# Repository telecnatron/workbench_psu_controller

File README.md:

# workbench_psu_controller
PSU controller comprising kicad PCB files, AVR C source files, python
utilities

see: https://telecnatron.com/articles/Workbench-Variable-PSU-15V-1A/index.html
for full details.

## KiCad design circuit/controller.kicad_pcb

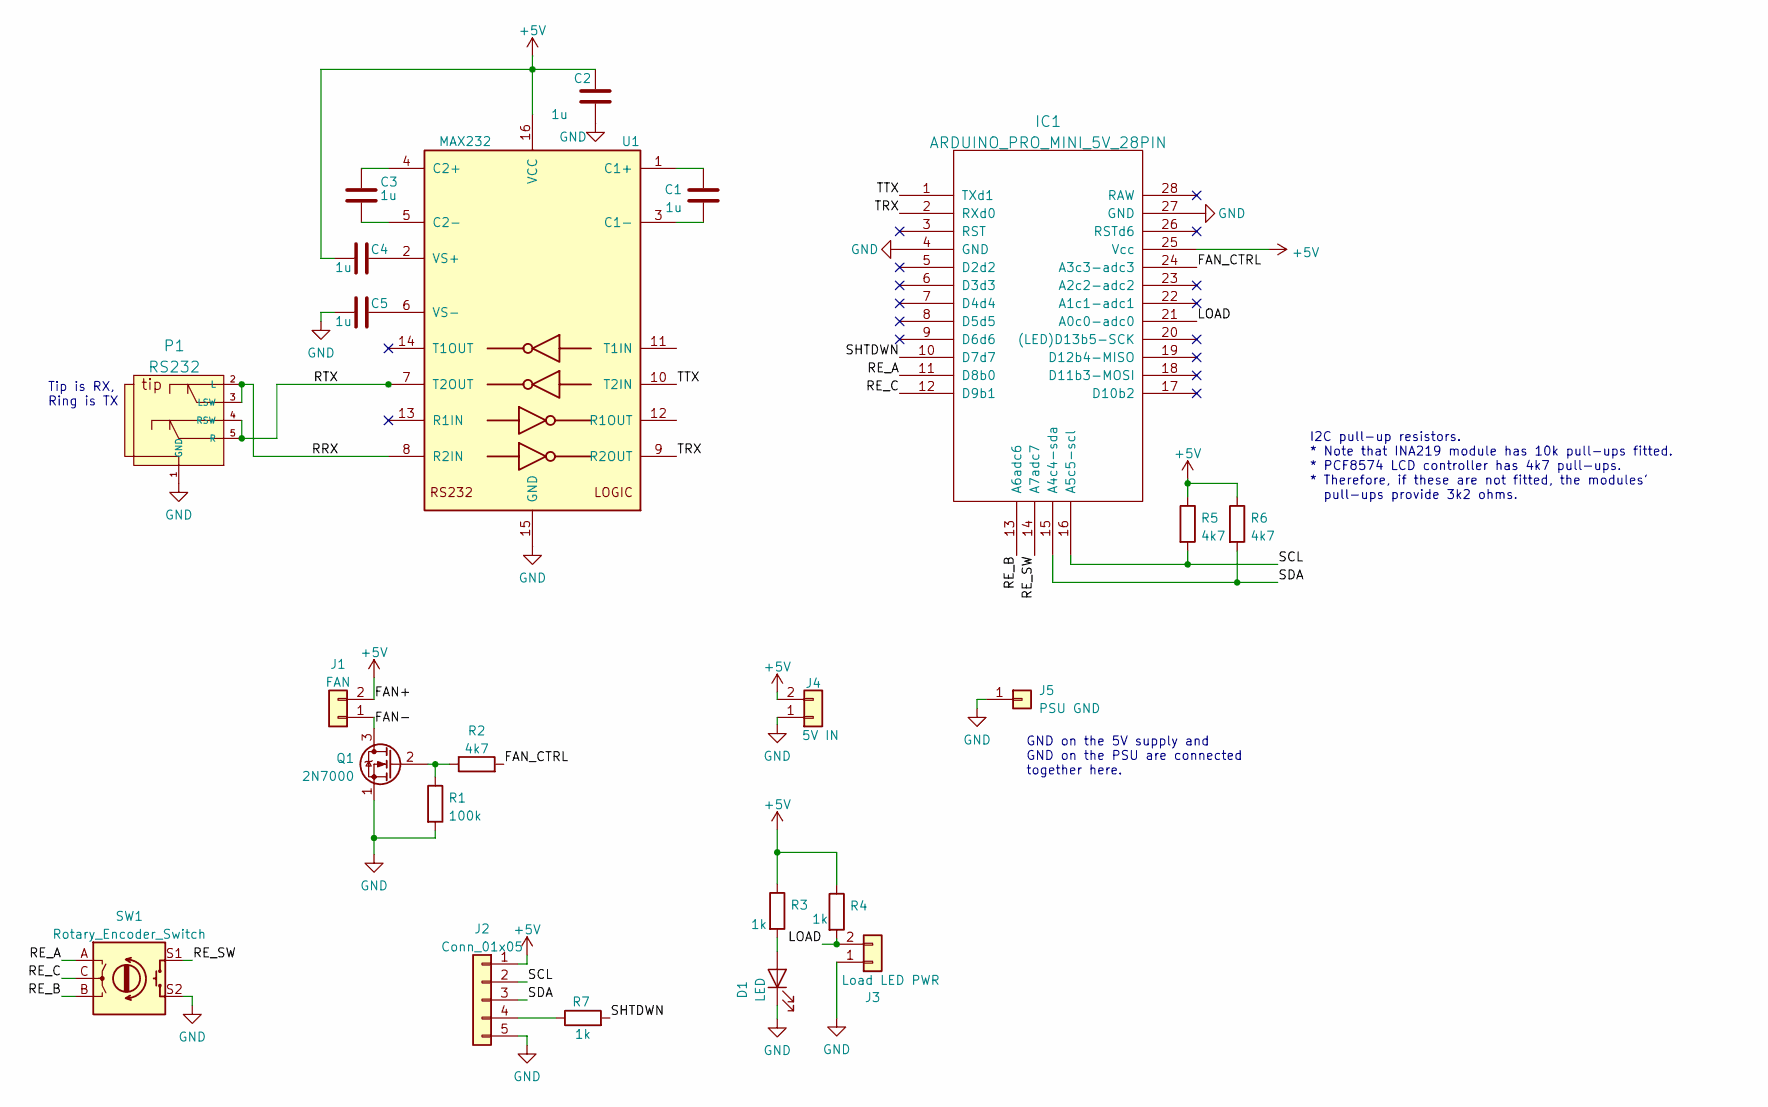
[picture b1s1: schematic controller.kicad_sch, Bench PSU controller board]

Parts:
C1, C2, C3, C4, C5: 1u; C_Disc_D6.0mm_W2.5mm_P5.00mm
D1: LED; JST_XH_B02B-XH-A_1x02_P2.50mm_Vertical
IC1: ARDUINO_PRO_MINI_5V_28PIN; DIP-28_W15.24mm_LongPads
J1: FAN; JST_XH_B02B-XH-A_1x02_P2.50mm_Vertical
J2: Conn_01x05; PinHeader_1x05_P2.54mm_Vertical
J3: Load LED PWR; JST_XH_B02B-XH-A_1x02_P2.50mm_Vertical
J4: 5V IN; JST_XH_B02B-XH-A_1x02_P2.50mm_Vertical
J5: PSU GND; PinHeader_1x01_P2.54mm_Vertical
P1: RS232; JACK-STEREO-3.5mm-PCB-HandSoldered
Q1: 2N7000; TO-92_Inline_Wide
R1: 100k; R_Axial_250mw_DIN0207_L6.3mm_D2.5mm_P10.16mm_Horizontal
R2, R5, R6: 4k7; R_Axial_250mw_DIN0207_L6.3mm_D2.5mm_P10.16mm_Horizontal
R3, R4, R7: 1k; R_Axial_250mw_DIN0207_L6.3mm_D2.5mm_P10.16mm_Horizontal
SW1: Rotary_Encoder_Switch; JST_XH_B5B-XH-AM_1x05_P2.50mm_Vertical_Rotary-Encoder
U1: MAX232; DIP-16_W7.62mm_Socket

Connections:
+5V: C2.1, C4.2, IC1.25 (Vcc), J1.2, J2.1, J4.2, R3.1, R4.1, R5.1, R6.1, U1.16 (VCC)
/FAN-: J1.1, Q1.3 (D)
/FAN_CTRL: IC1.24 (A3c3-adc3), R2.2
/LOAD: IC1.21 (A0c0-adc0), J3.2, R4.2
/RE_A: IC1.11 (D8b0), SW1.A (1)
/RE_B: IC1.13 (A6adc6), SW1.B (3)
/RE_C: IC1.12 (D9b1), SW1.C (2)
/RE_SW: IC1.14 (A7adc7), SW1.S1 (4)
/RRX: P1.2 (L), P1.3 (LSW), U1.8 (R2IN)
/RTX: P1.4 (RSW), P1.5 (R), U1.7 (T2OUT)
/SCL: IC1.16 (A5c5-scl), J2.2, R5.2
/SDA: IC1.15 (A4c4-sda), J2.3, R6.2
/SHTDWN: IC1.10 (D7d7), R7.2
/TRX: IC1.2 (RXd0), U1.9 (R2OUT)
/TTX: IC1.1 (TXd1), U1.10 (T2IN)
GND: C2.2, C5.2, D1.1 (K), IC1.4 (GND), IC1.27 (GND), J2.5, J3.1, J4.1, J5.1, P1.1 (GND), Q1.1 (S), R1.2, SW1.S2 (5), U1.15 (GND)
unnamed: C1.1, U1.1 (C1+)
unnamed: C1.2, U1.3 (C1-)
unnamed: C3.1, U1.4 (C2+)
unnamed: C3.2, U1.5 (C2-)
unnamed: C4.1, U1.2 (VS+)
unnamed: C5.1, U1.6 (VS-)
unnamed: D1.2 (A), R3.2
unnamed: J2.4, R7.1
unnamed: Q1.2 (G), R1.1, R2.1

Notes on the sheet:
Tip is RX, Ring is TX
GND on the 5V supply and GND on the PSU are connected together here.
I2C pull-up resistors. * Note that INA219 module has 10k pull-ups fitted. * PCF8574 LCD controller has 4k7 pull-ups. * Therefore, if these are not fitted, the modules' pull-ups provide 3k2 ohms.

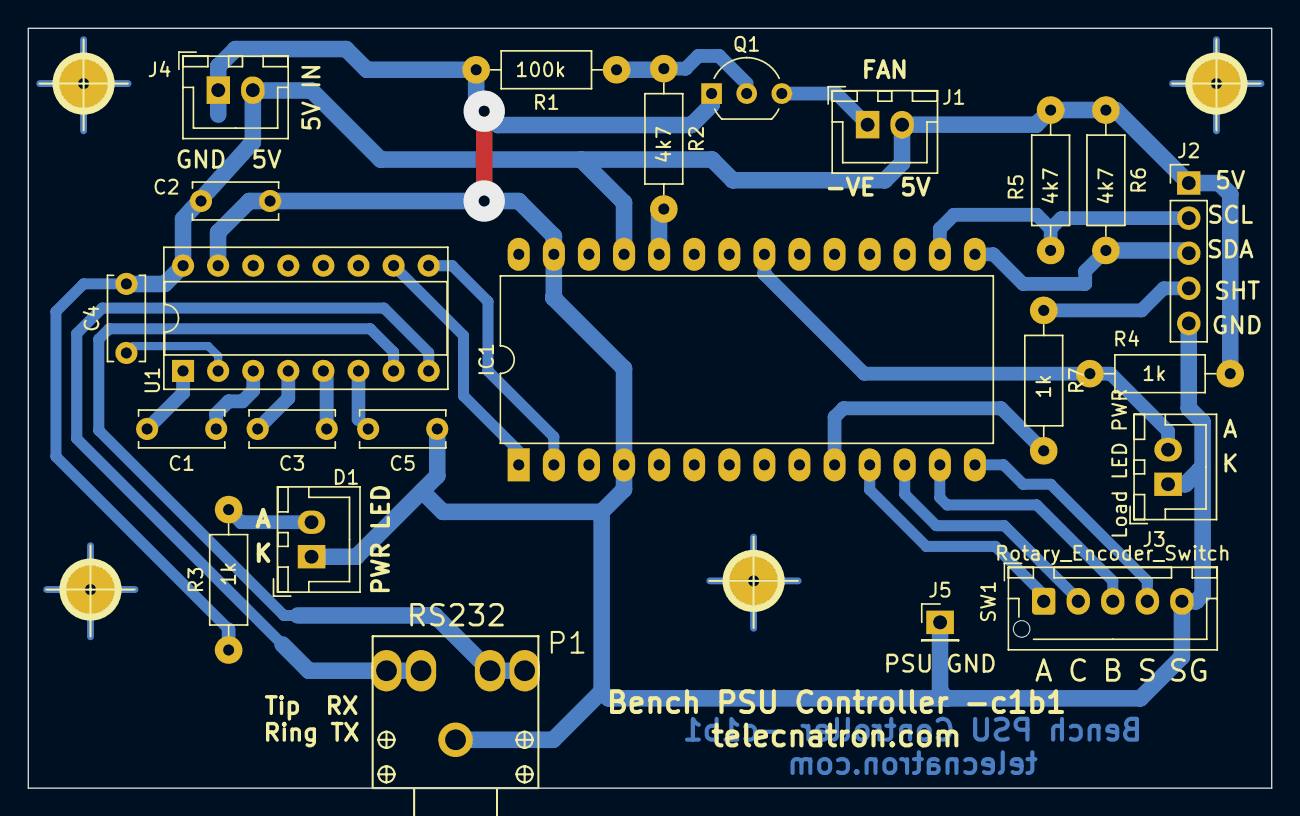
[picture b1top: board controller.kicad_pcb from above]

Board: 2 copper layers, 90.0 x 55.0 mm, 23 parts (0 on the bottom side), 25 nets.

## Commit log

2024-08-12 added README.md
